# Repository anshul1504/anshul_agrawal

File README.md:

#Personal Portfolio

- This is my personal portfolio. It was created on July 2020. In this project I have used HTML CSS & ES6 (Modern Javascript)
- 
- 👋 Hi, I’m Anshul Agrawal with username @anshul1504 
- 👀 I’m interested in web developement and freelancing 
- 🌱 I’m currently learning React-JS
- 💞️ I’m the founder of an instagram channel @the_webfix
- 📫 How to reach me -- @anshulagrawal1504@gmail.com

<!---
anshul1504/anshul_agrawal is a ✨ special ✨ repository because its `README.md` (this file) appears on your GitHub profile.
You can click the Preview link to take a look at your changes.
--->

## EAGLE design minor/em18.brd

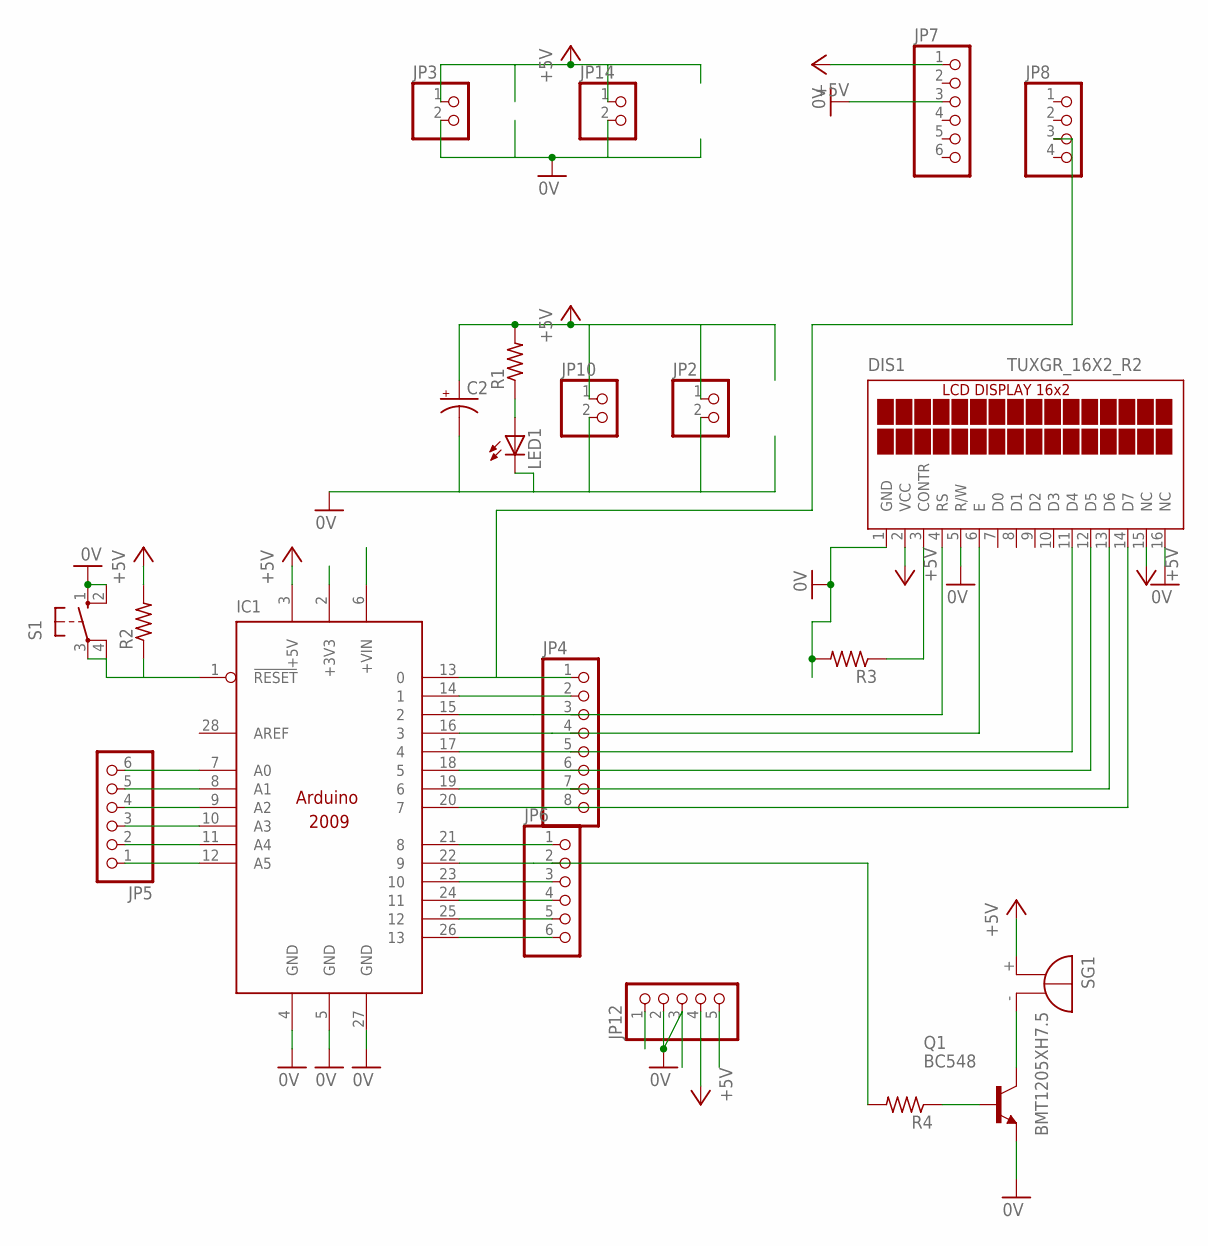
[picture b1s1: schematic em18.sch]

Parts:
C2: CPOL-USE3.5-10; E3,5-10
DIS1: TUXGR_16X2_R2
IC1: ARDUINO2009_10; ARDUINO2009
JP2, JP3, JP10, JP14: PINHD-1X2; 1X02
JP4: PINHD-1X8; 1X08
JP5, JP6, JP7: PINHD-1X6; 1X06
JP8: PINHD-1X4; 1X04
JP12: PINHD-1X5; 1X05
LED1: LED3MM
Q1: BC548; TO92-EBC
R1, R2, R3, R4: R-US_0207/7; 0207/7
S1: 10-XX; B3F-10XX
SG1: BMT1205XH7.5

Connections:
+5V: C2.+, DIS1.2 (VCC), DIS1.15 (NC), IC1.3 (+5V), JP2.1, JP3.1, JP7.1, JP10.1, JP12.4, JP14.1, R1.2, R2.2, SG1.+
unnamed: C2.-, DIS1.1 (GND), DIS1.5 (R/W), DIS1.16 (NC), IC1.4 (GND), IC1.5 (GND), IC1.27 (GND), JP2.2, JP3.2, JP7.3, JP10.2, JP12.2, JP12.3, JP14.2, LED1.K (C), Q1.E, R3.2, S1.1 (S), S1.2 (S1)
unnamed: IC1.2 (+3V3), JP12.5
unnamed: Q1.C, SG1.-
unnamed: Q1.B, R4.1
unnamed: LED1.A, R1.1
unnamed: IC1.1 (!RESET), R2.1, S1.3, S1.4 (P1)
unnamed: IC1.6 (+VIN), JP12.1
unnamed: IC1.13 (0), JP4.1, JP8.3
unnamed: IC1.14 (1), JP4.2
unnamed: IC1.12 (A5), JP5.1
unnamed: IC1.11 (A4), JP5.2
unnamed: IC1.10 (A3), JP5.3
unnamed: IC1.9 (A2), JP5.4
unnamed: IC1.8 (A1), JP5.5
unnamed: IC1.7 (A0), JP5.6
unnamed: IC1.21 (8), JP6.1
unnamed: IC1.22 (9), JP6.2, R4.2
unnamed: IC1.23 (10), JP6.3
unnamed: IC1.24 (11), JP6.4
unnamed: IC1.25 (12), JP6.5
unnamed: IC1.26 (13), JP6.6
unnamed: DIS1.3 (CONTR), R3.1
unnamed: DIS1.4 (RS), IC1.15 (2), JP4.3
unnamed: DIS1.6 (E), IC1.16 (3), JP4.4
unnamed: DIS1.11 (D4), IC1.17 (4), JP4.5
unnamed: DIS1.12 (D5), IC1.18 (5), JP4.6
unnamed: DIS1.13 (D6), IC1.19 (6), JP4.7
unnamed: DIS1.14 (D7), IC1.20 (7), JP4.8

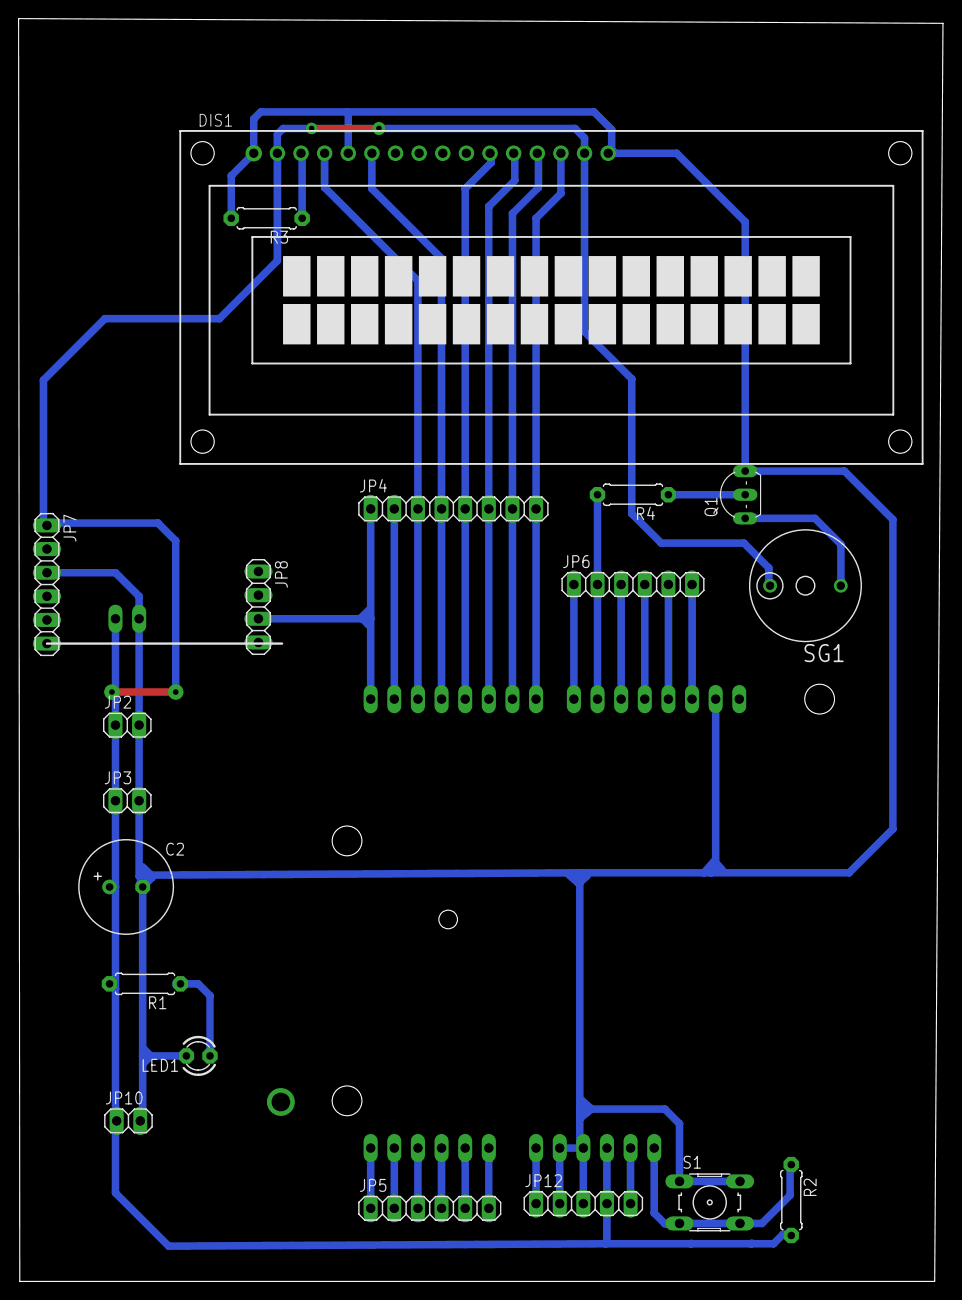
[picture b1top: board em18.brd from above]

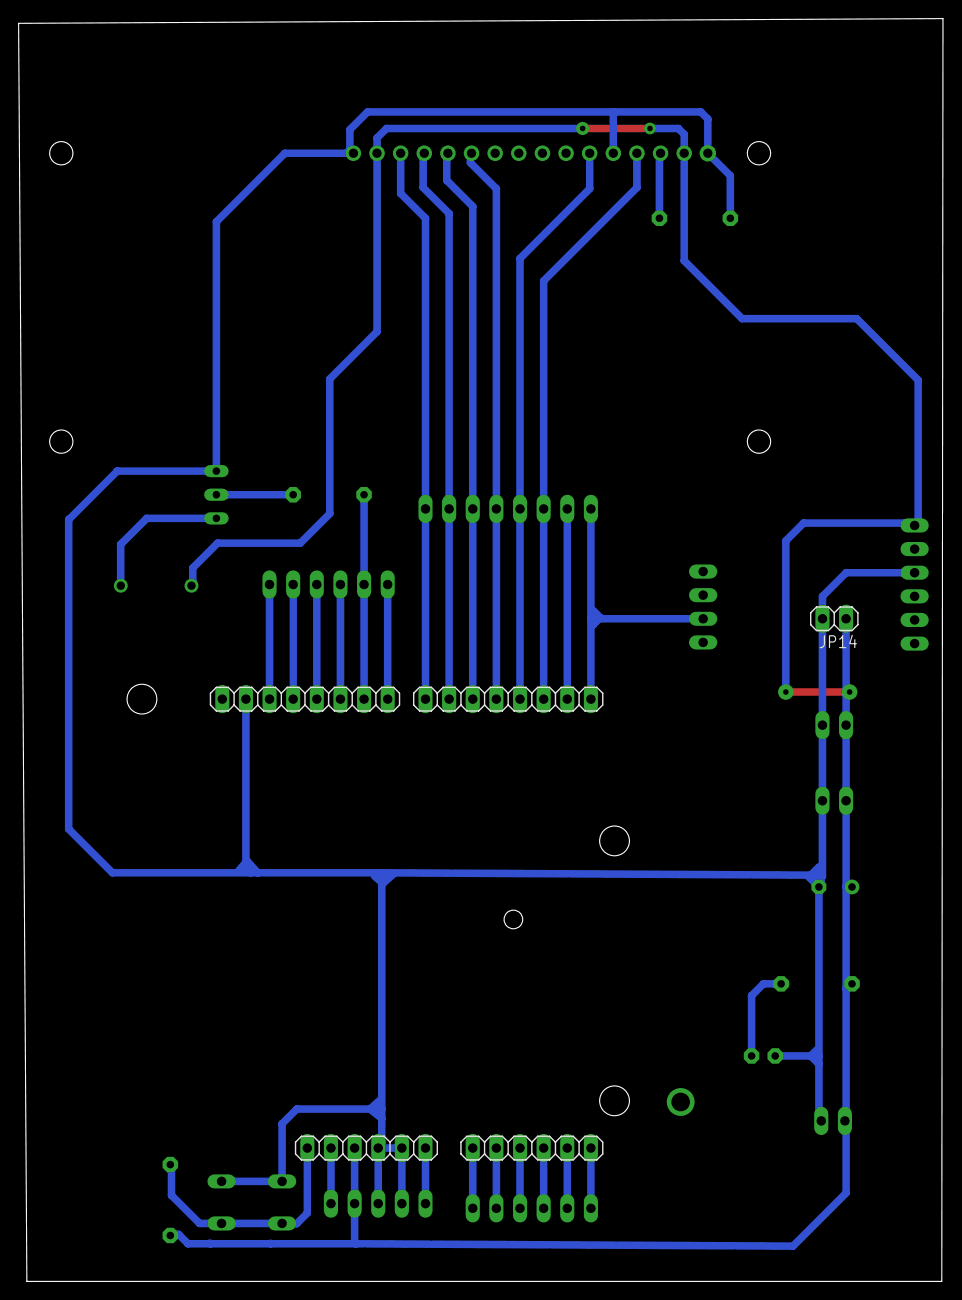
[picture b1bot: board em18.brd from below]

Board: 2 copper layers, 99.4 x 135.7 mm, 21 parts (2 on the bottom side), 29 nets.
